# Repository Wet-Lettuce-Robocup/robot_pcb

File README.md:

# Wet Lettuce Robot PCB

Kicad design file for the Wet Lettuce RoboCup Junior International robot.

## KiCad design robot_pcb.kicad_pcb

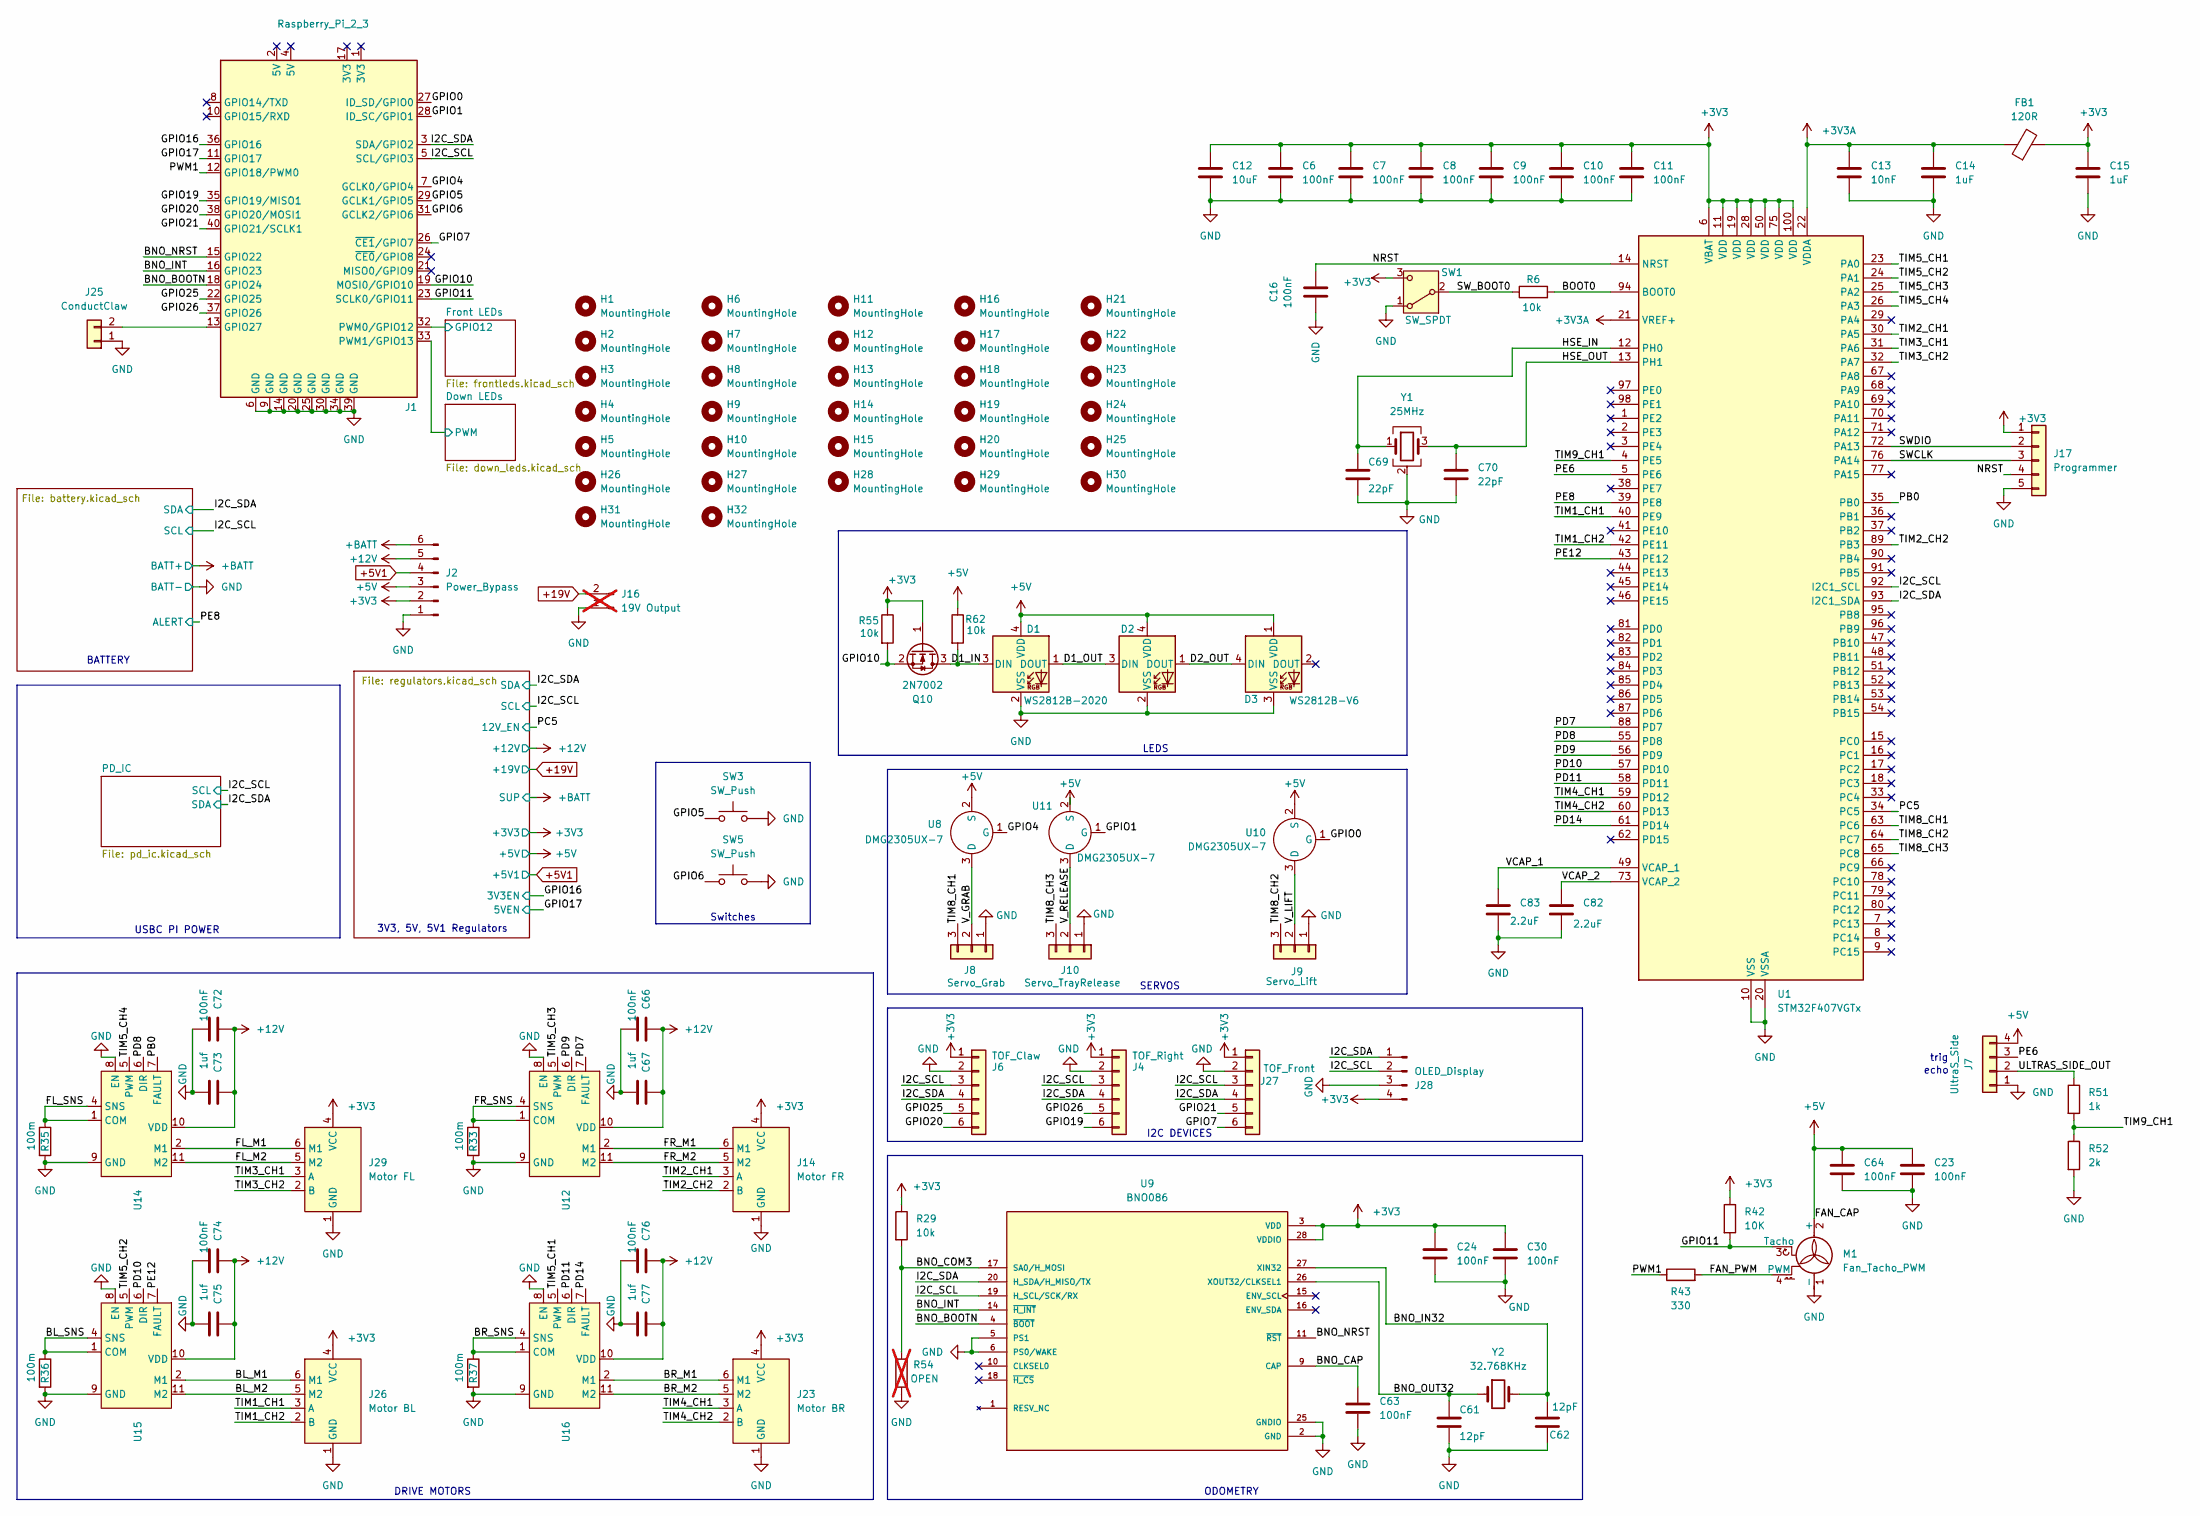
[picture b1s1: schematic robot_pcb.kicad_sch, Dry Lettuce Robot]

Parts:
C6, C7, C8, C9, C10, C11, C16, C23, C24, C30, C63, C64: 100nF; C_0402_1005Metric; LCSC C307331
C12: 10uF; C_0603_1608Metric; LCSC C96446
C13: 10nF; C_0402_1005Metric; LCSC C15195
C14, C15: 1uF; C_0402_1005Metric; LCSC C52923
C61, C62: 12pF; C_0402_1005Metric; LCSC C76948
C66, C72, C74, C76: 100nF; C_0603_1608Metric; LCSC C14663
C67, C73, C75, C77: 1uf; C_0603_1608Metric; LCSC C29936
C69, C70: 22pF; C_0402_1005Metric; LCSC C76960
C82, C83: 2.2uF; C_0603_1608Metric; LCSC C23630
D1, D2: WS2812B-2020; LED_WS2812B-2020_PLCC4_2.0x2.0mm; LCSC C965555
D3: WS2812B-V6; LED_WS2812B_PLCC4_5.0x5.0mm_P3.2mm; LCSC C52917433
FB1: 120R; L_0603_1608Metric; LCSC C113030
H1, H2, H3, H4, H13, H14, H15, H20, H21, H22, H23, H30: MountingHole; MountingHole_3.2mm_M3_DIN965_Pad_TopBottom
H5, H6, H7, H8, H18, H19, H28, H29: MountingHole; MountingHole_2.2mm_M2_DIN965_Pad_TopBottom
H9, H10, H11, H12, H16, H17, H24, H25, H26, H27, H31, H32: MountingHole; MountingHole_2.7mm_M2.5_DIN965_Pad_TopBottom
J1: Raspberry_Pi_2_3; PinHeader_2x20_P2.54mm_Vertical; LCSC C50980
J2: Power_Bypass; PinHeader_1x06_P2.54mm_Vertical; LCSC C52016393
J4: TOF_Right; JST_PH_B6B-PH-K_1x06_P2.00mm_Vertical; LCSC C495261
J6: TOF_Claw; JST_PH_B6B-PH-K_1x06_P2.00mm_Vertical; LCSC C495261
J7: UltraS_Side; PinHeader_1x04_P2.54mm_Vertical; LCSC C541851
J8: Servo_Grab; JST_PH_B3B-PH-K_1x03_P2.00mm_Vertical; LCSC C158004
J9: Servo_Lift; JST_PH_B3B-PH-K_1x03_P2.00mm_Vertical; LCSC C158004
J10: Servo_TrayRelease; JST_PH_B3B-PH-K_1x03_P2.00mm_Vertical; LCSC C158004
J14: Motor FR; JST_PH_S6B-PH-K_1x06_P2.00mm_Horizontal; LCSC C157920
J16: 19V Output; JST_VH_B2PS-VH_1x02_P3.96mm_Horizontal; LCSC C158007; not fitted
J17: Programmer; PinHeader_1x05_P2.54mm_Vertical; LCSC C42431835
J23: Motor BR; JST_PH_S6B-PH-K_1x06_P2.00mm_Horizontal; LCSC C157920
J25: ConductClaw; JST_PH_B2B-PH-K_1x02_P2.00mm_Vertical; LCSC C5251182
J26: Motor BL; JST_PH_S6B-PH-K_1x06_P2.00mm_Horizontal; LCSC C157920
J27: TOF_Front; JST_PH_B6B-PH-K_1x06_P2.00mm_Vertical; LCSC C495261
J28: OLED_Display; OLED_small; LCSC C2718488
J29: Motor FL; JST_PH_S6B-PH-K_1x06_P2.00mm_Horizontal; LCSC C157920
M1: Fan_Tacho_PWM; FanPinHeader_1x04_P2.54mm_Vertical; LCSC C240840
Q10: 2N7002; SOT-23; LCSC C65189
R6, R29, R55, R62: 10k; R_0402_1005Metric; LCSC C60490
R33, R35, R36, R37: 100m; R_1206_3216Metric; LCSC C3033268
R42: 10K; R_0402_1005Metric; LCSC C60490
R43: 330; R_0402_1005Metric; LCSC C105875
R51: 1k; R_0603_1608Metric; LCSC C22548
R52: 2k; R_0603_1608Metric; LCSC C105576
R54: OPEN; R_0402_1005Metric; not fitted
SW1: SW_SPDT; SW_Slide_SPDT_Straight_CK_OS102011MS2Q; LCSC C221829
SW3, SW5: SW_Push; SW_Push_1P1T_NO_CK_new; LCSC C431539
U1: STM32F407VGTx; LQFP-100_14x14mm_P0.5mm; LCSC C720656
U8, U10, U11: DMG2305UX-7; TSOT-23; LCSC C150470
U9: BNO086; IC_BNO086; PARTREV v1.17; LCSC C5264422
U12, U14, U15, U16: Maxim_TDFN-12-1EP_3x3mm_P0.5mm_EP1.7x2.5mm; LCSC C194048
Y1: 25MHz; Crystal_SMD_3225-4Pin_3.2x2.5mm; LCSC C5444544
Y2: 32.768KHz; Crystal_SMD_3215-2Pin_3.2x1.5mm; LCSC C99010

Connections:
+3V3: C6.1, C7.1, C8.1, C9.1, C10.1, C11.1, C12.1, C15.1, C24.1, C30.1, FB1.2, J2.2, J4.1, J6.1, J14.4 (VCC), J17.1, J23.4 (VCC), J26.4 (VCC), J27.1, J28.4, J29.4 (VCC), Q10.1 (G), R29.1, R42.1, R55.1, SW1.3 (C), U1.6 (VBAT), U1.11 (VDD), U1.19 (VDD), U1.28 (VDD), U1.50 (VDD), U1.75 (VDD), U1.100 (VDD), U9.3 (VDD), U9.28 (VDDIO); also elsewhere on the board
+3V3A: C13.1, C14.1, FB1.1, U1.21 (VREF+), U1.22 (VDDA)
+5V: C23.1, C64.1, D1.4 (VDD), D2.4 (VDD), D3.1 (VDD), J2.3, J7.4, M1.2 (+), R62.1, U8.2 (S), U10.2 (S), U11.2 (S); also elsewhere on the board
+5V1: J2.4; also elsewhere on the board
+12V: C66.1, C67.1, C72.1, C73.1, C74.1, C75.1, C76.1, C77.1, J2.5, U12.3 (VDD), U12.10 (VDD), U14.3 (VDD), U14.10 (VDD), U15.3 (VDD), U15.10 (VDD), U16.3 (VDD), U16.10 (VDD); also elsewhere on the board
+19V: J16.2; also elsewhere on the board
+BATT: J2.6; also elsewhere on the board
/BL_M1: J26.6 (M1), U15.2 (M1)
/BL_M2: J26.5 (M2), U15.11 (M2)
/BL_SNS: R36.1, U15.1 (COM), U15.4 (SNS), U15.12 (COM)
/BNO_BOOTN: J1.18 (GPIO24), U9.4 (~BOOT)
/BNO_CAP: C63.1, U9.9 (CAP)
/BNO_COM3: R29.2, R54.1, U9.17 (SA0/H_MOSI)
/BNO_IN32: C62.1, U9.27 (XIN32), Y2.2
/BNO_INT: J1.16 (GPIO23), U9.14 (~H_INT)
/BNO_NRST: J1.15 (GPIO22), U9.11 (~RST)
/BNO_OUT32: C61.1, U9.26 (XOUT32/CLKSEL1), Y2.1
/BOOT0: R6.2, U1.94 (BOOT0)
/BR_M1: J23.6 (M1), U16.2 (M1)
/BR_M2: J23.5 (M2), U16.11 (M2)
/BR_SNS: R37.1, U16.1 (COM), U16.4 (SNS), U16.12 (COM)
/D1_IN: D1.3 (DIN), Q10.3 (D), R62.2
/D1_OUT: D1.1 (DOUT), D2.3 (DIN)
/D2_OUT: D2.1 (DOUT), D3.4 (DIN)
/Down LEDs/PWM: J1.33 (PWM1/GPIO13); also elsewhere on the board
/FAN_PWM: M1.4 (PWM), R43.2
/FL_M1: J29.6 (M1), U14.2 (M1)
/FL_M2: J29.5 (M2), U14.11 (M2)
/FL_SNS: R35.1, U14.1 (COM), U14.4 (SNS), U14.12 (COM)
/FR_M1: J14.6 (M1), U12.2 (M1)
/FR_M2: J14.5 (M2), U12.11 (M2)
/FR_SNS: R33.1, U12.1 (COM), U12.4 (SNS), U12.12 (COM)
/Front LEDs/GPIO12: J1.32 (PWM0/GPIO12); also elsewhere on the board
/GPIO0: J1.27 (ID_SD/GPIO0), U10.1 (G)
/GPIO1: J1.28 (ID_SC/GPIO1), U11.1 (G)
/GPIO4: J1.7 (GCLK0/GPIO4), U8.1 (G)
/GPIO5: J1.29 (GCLK1/GPIO5), SW3.1
/GPIO6: J1.31 (GCLK2/GPIO6), SW5.1
/GPIO7: J1.26 (~CE1/GPIO7), J27.6
/GPIO10: J1.19 (MOSI0/GPIO10), Q10.2 (S), R55.2
/GPIO11: J1.23 (SCLK0/GPIO11), M1.3 (Tacho), R42.2
/GPIO16: J1.36 (GPIO16); also elsewhere on the board
/GPIO17: J1.11 (GPIO17); also elsewhere on the board
/GPIO19: J1.35 (GPIO19/MISO1), J4.6
/GPIO20: J1.38 (GPIO20/MOSI1), J6.6
/GPIO21: J1.40 (GPIO21/SCLK1), J27.5
/GPIO25: J1.22 (GPIO25), J6.5
/GPIO26: J1.37 (GPIO26), J4.5
/HSE_IN: C69.1, U1.12 (PH0), Y1.1
/HSE_OUT: C70.1, U1.13 (PH1), Y1.3
/I2C_SCL: J1.5 (SCL/GPIO3), J4.3, J6.3, J27.3, J28.2, U1.92 (I2C1_SCL), U9.19 (H_SCL/SCK/RX); also elsewhere on the board
/I2C_SDA: J1.3 (SDA/GPIO2), J4.4, J6.4, J27.4, J28.1, U1.93 (I2C1_SDA), U9.20 (H_SDA/H_MISO/TX); also elsewhere on the board
/NRST: C16.2, J17.4, U1.14 (NRST)
/PB0: U1.35 (PB0), U14.7 (FAULT)
/PC5: U1.34 (PC5); also elsewhere on the board
/PD7: U1.88 (PD7), U12.7 (FAULT)
/PD8: U1.55 (PD8), U14.6 (DIR)
/PD9: U1.56 (PD9), U12.6 (DIR)
/PD10: U1.57 (PD10), U15.6 (DIR)
/PD11: U1.58 (PD11), U16.6 (DIR)
/PD14: U1.61 (PD14), U16.7 (FAULT)
/PE6: J7.3, U1.5 (PE6)
/PE8: U1.39 (PE8); also elsewhere on the board
/PE12: U1.43 (PE12), U15.7 (FAULT)
/PWM1: J1.12 (GPIO18/PWM0), R43.1
/SWCLK: J17.3, U1.76 (PA14)
/SWDIO: J17.2, U1.72 (PA13)
/SW_BOOT0: R6.1, SW1.2 (B)
/TIM1_CH1: J26.3 (A), U1.40 (PE9)
/TIM1_CH2: J26.2 (B), U1.42 (PE11)
/TIM2_CH1: J14.3 (A), U1.30 (PA5)
/TIM2_CH2: J14.2 (B), U1.89 (PB3)
/TIM3_CH1: J29.3 (A), U1.31 (PA6)
/TIM3_CH2: J29.2 (B), U1.32 (PA7)
/TIM4_CH1: J23.3 (A), U1.59 (PD12)
/TIM4_CH2: J23.2 (B), U1.60 (PD13)
/TIM5_CH1: U1.23 (PA0), U16.5 (PWM)
/TIM5_CH2: U1.24 (PA1), U15.5 (PWM)
/TIM5_CH3: U1.25 (PA2), U12.5 (PWM)
/TIM5_CH4: U1.26 (PA3), U14.5 (PWM)
/TIM8_CH1: J8.3, U1.63 (PC6)
/TIM8_CH2: J9.3, U1.64 (PC7)
/TIM8_CH3: J10.3, U1.65 (PC8)
/TIM9_CH1: R51.2, R52.1, U1.4 (PE5)
/ULTRAS_SIDE_OUT: J7.2, R51.1
/VCAP_1: C83.1, U1.49 (VCAP_1)
/VCAP_2: C82.1, U1.73 (VCAP_2)
/V_GRAB: J8.2, U8.3 (D)
/V_LIFT: J9.2, U10.3 (D)
/V_RELEASE: J10.2, U11.3 (D)
GND: C6.2, C7.2, C8.2, C9.2, C10.2, C11.2, C12.2, C13.2, C14.2, C15.2, C16.1, C23.2, C24.2, C30.2, C61.2, C62.2, C63.2, C64.2, C66.2, C67.2, C69.2, C70.2, C72.2, C73.2, C74.2, C75.2, C76.2, C77.2, C82.2, C83.2, D1.2 (VSS), D2.2 (VSS), D3.3 (VSS), J1.6 (GND), J1.9 (GND), J1.14 (GND), J1.20 (GND), J1.25 (GND), J1.30 (GND), J1.34 (GND), J1.39 (GND), J2.1, J4.2, J6.2, J7.1, J8.1, J9.1, J10.1, J14.1 (GND), J16.1, J17.5, J23.1 (GND), J25.1, J26.1 (GND), J27.2, J28.3, J29.1 (GND), M1.1 (-), R33.2, R35.2, R36.2, R37.2, R52.2, R54.2, SW1.1 (A), SW3.2, SW5.2, U1.10 (VSS), U1.20 (VSSA), U1.27 (VSS), U1.74 (VSS), U1.99 (VSS), U9.2 (GND), U9.5 (PS1), U9.6 (PS0/WAKE), U9.25 (GNDIO), U12.8 (EN), U12.9 (GND), U12.13 (PAD), U14.8 (EN), U14.9 (GND), U14.13 (PAD), U15.8 (EN), U15.9 (GND), U15.13 (PAD), U16.8 (EN), U16.9 (GND), U16.13 (PAD), Y1.2 (G), Y1.4 (G); also elsewhere on the board
unnamed: J1.13 (GPIO27), J25.2

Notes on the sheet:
LEDS
ODOMETRY
trig
SERVOS
USBC PI POWER
DRIVE MOTORS
BATTERY
3V3, 5V, 5V1 Regulators
Switches
I2C DEVICES
echo

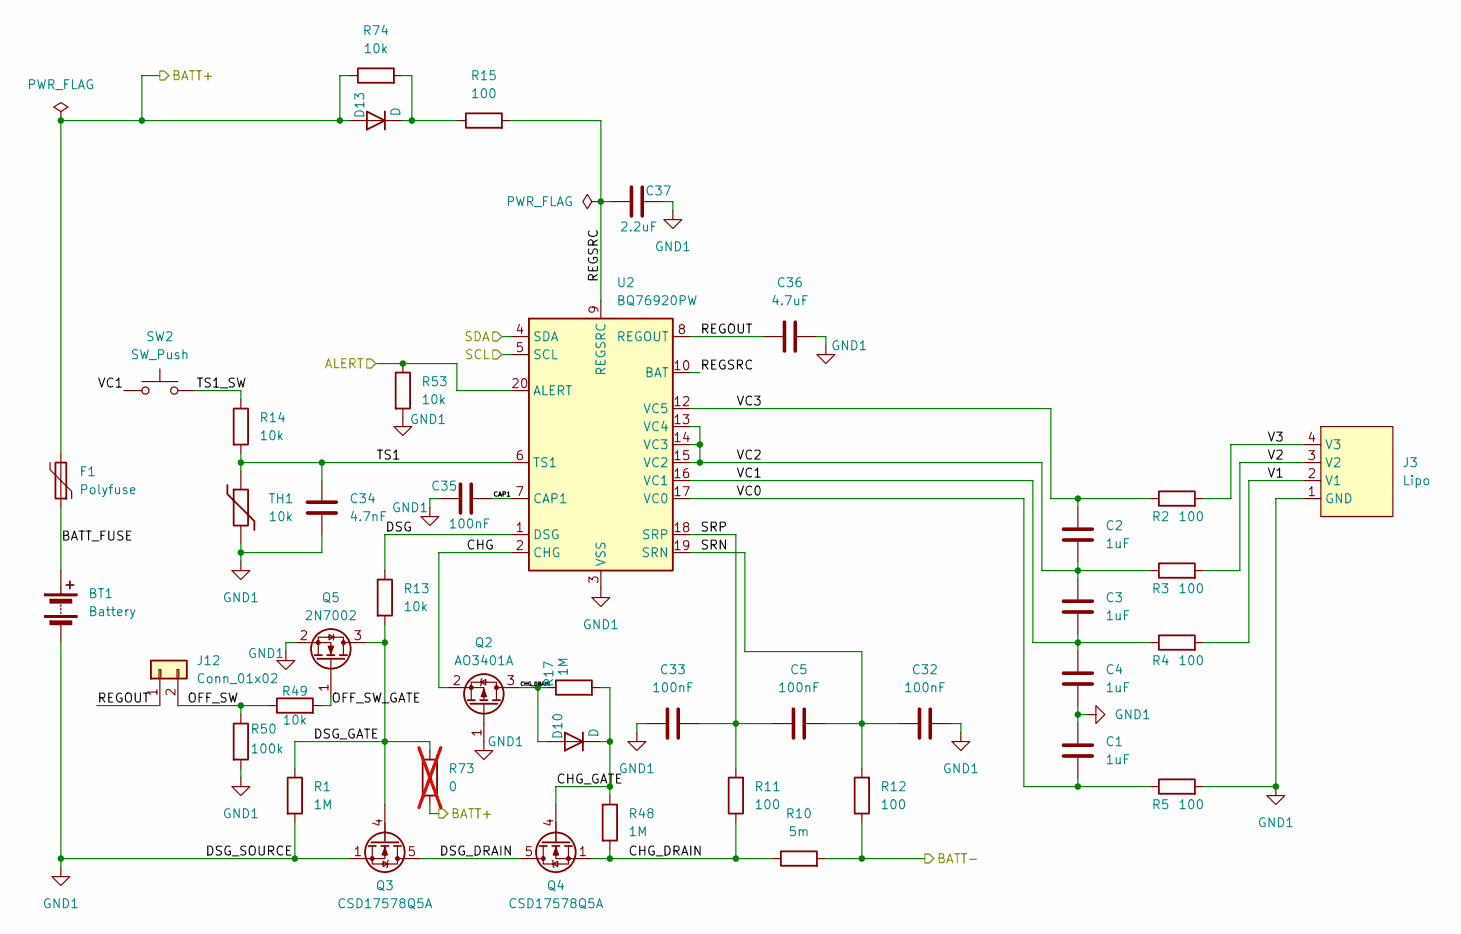
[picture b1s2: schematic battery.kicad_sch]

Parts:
BT1: Battery; AMASS_XT60-M_1x02_P7.20mm_Vertical; LCSC C98733
C1, C2, C3, C4: 1uF; C_0402_1005Metric; LCSC C52923
C5, C32, C33, C35: 100nF; C_0402_1005Metric; LCSC C307331
C34: 4.7nF; C_0402_1005Metric; LCSC C84705
C36: 4.7uF; C_0603_1608Metric; LCSC C69335
C37: 2.2uF; C_0402_1005Metric; LCSC C307418
D10, D13: D; D_0603_1608Metric; LCSC C35621074
F1: Polyfuse; Fuse_Bourns_MF-RG900; LCSC C3762600
J3: Lipo; JST_XH_B4B-XH-A_1x04_P2.50mm_Vertical; LCSC C594232
J12: Conn_01x02; JST_PH_S2B-PH-K_1x02_P2.00mm_Horizontal; LCSC C173752
Q2: AO3401A; SOT-23; LCSC C15127
Q3, Q4: CSD17578Q5A; TDSON-8-1; LCSC C2871447
Q5: 2N7002; SOT-23; LCSC C65189
R1, R17, R48: 1M; R_0402_1005Metric; LCSC C138033
R2, R3, R4, R5: 100; R_0805_2012Metric; LCSC C105577
R10: 5m; R_2512_6332Metric; LCSC C2903482
R11, R12: 100; R_0603_1608Metric; LCSC C105588
R13, R14, R49, R53, R74: 10k; R_0402_1005Metric; LCSC C60490
R15: 100; R_1206_3216Metric; LCSC C2907369
R50: 100k; R_0402_1005Metric; LCSC C60491
R73: 0; R_0402_1005Metric; LCSC C60490; not fitted
SW2: SW_Push; SW_Push_1P1T_NO_CK_new; LCSC C431539
TH1: 10k; R_0402_1005Metric; LCSC C209959
U2: BQ76920PW; TSSOP-20_4.4x6.5mm_P0.65mm; LCSC C601650

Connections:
+BATT: D13.2 (A), F1.2, R73.2, R74.1; also elsewhere on the board
/Battery/BATT_FUSE: BT1.1 (+), F1.1
/Battery/CAP1: C35.2, U2.7 (CAP1)
/Battery/CHG: Q2.2 (S), U2.2 (CHG)
/Battery/CHG_DRAIN: D10.2 (A), Q2.3 (D), Q4.1 (S), Q4.2 (S), Q4.3 (S), R10.1, R11.1, R17.1, R48.2
/Battery/CHG_GATE: D10.1 (K), Q4.4 (G), R17.2, R48.1
/Battery/DSG: R13.1, U2.1 (DSG)
/Battery/DSG_DRAIN: Q3.5 (D), Q4.5 (D)
/Battery/DSG_GATE: Q3.4 (G), Q5.3 (D), R1.1, R13.2, R73.1
/Battery/OFF_SW: J12.2, R49.1, R50.1
/Battery/OFF_SW_GATE: Q5.1 (G), R49.2
/Battery/REGOUT: C36.1, J12.1, U2.8 (REGOUT)
/Battery/REGSRC: C37.1, R15.2, U2.9 (REGSRC), U2.10 (BAT)
/Battery/SRN: C5.2, C32.1, R12.2, U2.19 (SRN)
/Battery/SRP: C5.1, C33.2, R11.2, U2.18 (SRP)
/Battery/TS1: C34.1, R14.2, TH1.1, U2.6 (TS1)
/Battery/TS1_SW: R14.1, SW2.2
/Battery/V1: J3.2 (V1), R4.2
/Battery/V2: J3.3 (V2), R3.2
/Battery/V3: J3.4 (V3), R2.2
/Battery/VC0: C1.2, R5.1, U2.17 (VC0)
/Battery/VC1: C3.2, C4.1, R4.1, SW2.1, U2.16 (VC1)
/Battery/VC2: C2.2, C3.1, R3.1, U2.13 (VC4), U2.14 (VC3), U2.15 (VC2)
/Battery/VC3: C2.1, R2.1, U2.12 (VC5)
/I2C_SCL: U2.5 (SCL); also elsewhere on the board
/I2C_SDA: U2.4 (SDA); also elsewhere on the board
/PE8: R53.1, U2.20 (ALERT); also elsewhere on the board
GND: R10.2, R12.1; also elsewhere on the board
GND1: BT1.2 (-), C1.1, C4.2, C32.2, C33.1, C34.2, C35.1, C36.2, C37.2, J3.1 (GND), Q2.1 (G), Q3.1 (S), Q3.2 (S), Q3.3 (S), Q5.2 (S), R1.2, R5.2, R50.2, R53.2, TH1.2, U2.3 (VSS)
unnamed: D13.1 (K), R15.1, R74.2

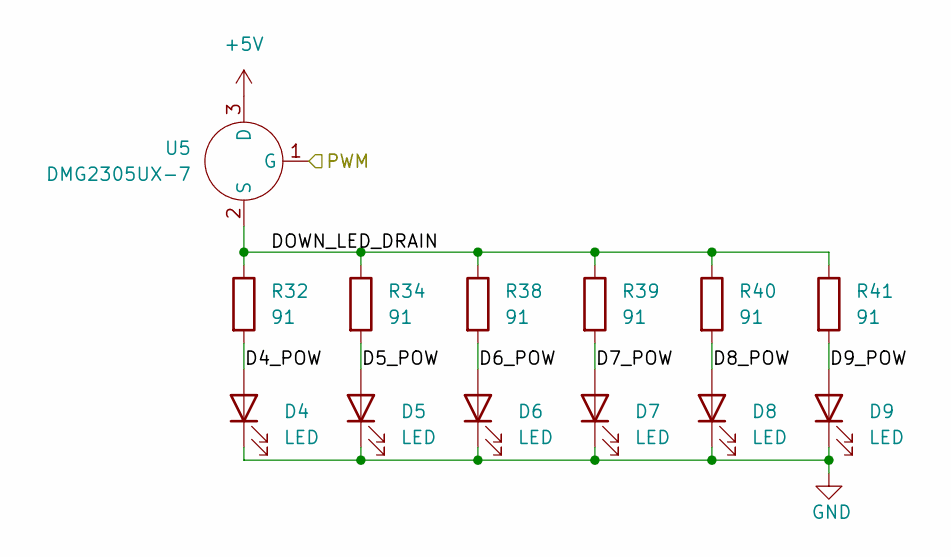
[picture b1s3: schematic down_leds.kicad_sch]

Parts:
D4, D5, D6, D7, D8, D9: LED; LED_PLCC_2835; LCSC C2843876
R32, R34, R38, R39, R40, R41: 91; R_1206_3216Metric; LCSC C5842965
U5: DMG2305UX-7; TSOT-23; LCSC C150470

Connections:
+5V: U5.3 (D); also elsewhere on the board
/Down LEDs/D4_POW: D4.2 (A), R32.2
/Down LEDs/D5_POW: D5.2 (A), R34.2
/Down LEDs/D6_POW: D6.2 (A), R38.2
/Down LEDs/D7_POW: D7.2 (A), R39.2
/Down LEDs/D8_POW: D8.2 (A), R40.2
/Down LEDs/D9_POW: D9.2 (A), R41.2
/Down LEDs/DOWN_LED_DRAIN: R32.1, R34.1, R38.1, R39.1, R40.1, R41.1, U5.2 (S)
/Down LEDs/PWM: U5.1 (G); also elsewhere on the board
GND: D4.1 (K), D5.1 (K), D6.1 (K), D7.1 (K), D8.1 (K), D9.1 (K); also elsewhere on the board

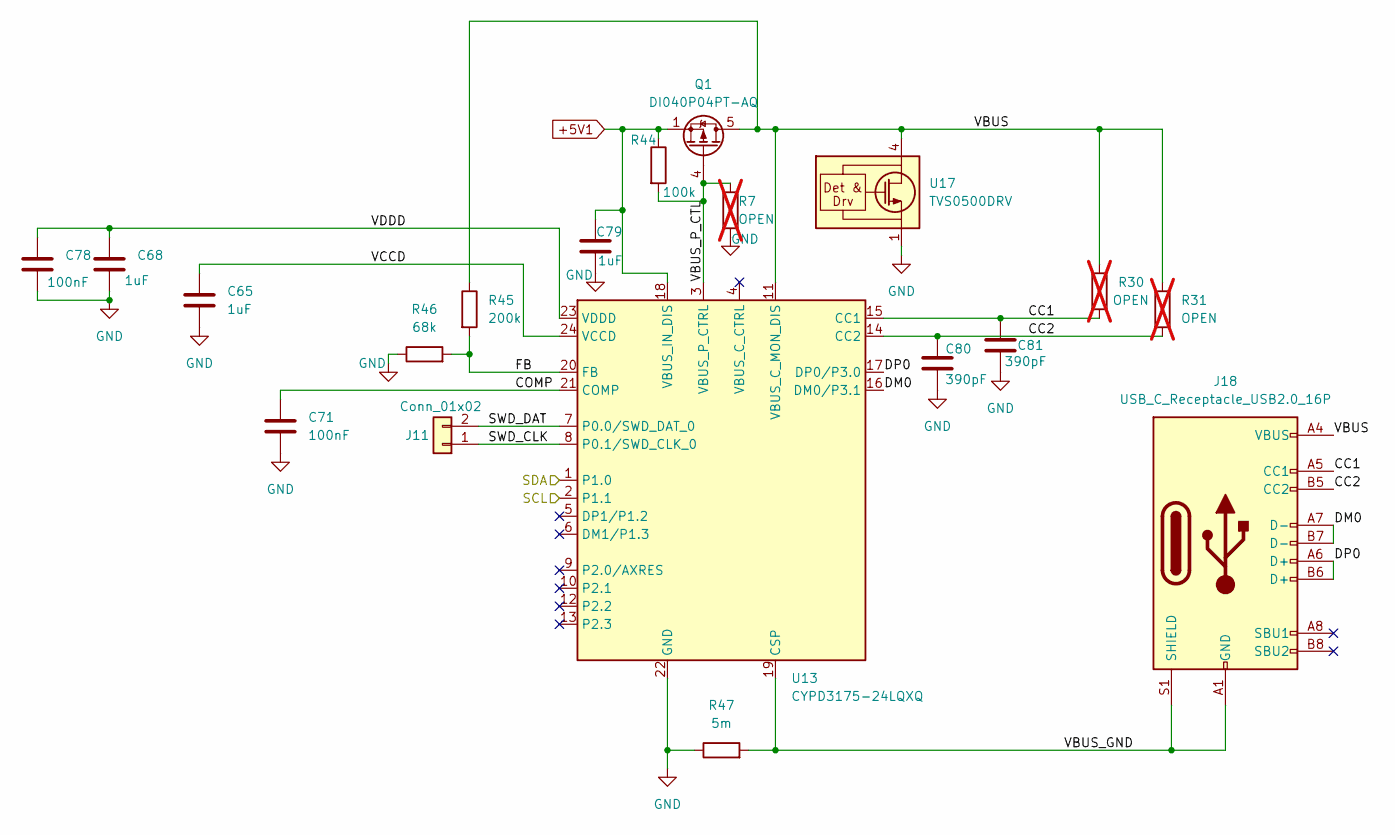
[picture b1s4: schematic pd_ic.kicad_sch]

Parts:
C65, C68, C79: 1uF; C_0402_1005Metric; LCSC C52923
C71, C78: 100nF; C_0402_1005Metric; LCSC C307331
C80, C81: 390pF; C_0402_1005Metric; LCSC C114397
J11: Conn_01x02; PinHeader_1x02_P2.54mm_Vertical; LCSC C52016390
J18: USB_C_Receptacle_USB2.0_16P; USB_C_Receptacle_GCT_USB4105-xx-A_16P_TopMnt_Horizontal; LCSC C3025063
Q1: DI040P04PT-AQ; Vishay_PowerPAK_1212-8_Single; LCSC C6934675
R7, R30, R31: OPEN; R_0402_1005Metric; not fitted
R44: 100k; R_0402_1005Metric; LCSC C60491
R45: 200k; R_0402_1005Metric; LCSC C114763
R46: 68k; R_0402_1005Metric; LCSC C137947
R47: 5m; R_2512_6332Metric; LCSC C2903482
U13: CYPD3175-24LQXQ; QFN-24-1EP_4x4mm_P0.5mm_EP2.75x2.75mm; LCSC C2952419
U17: TVS0500DRV; WSON-6-1EP_2x2mm_P0.65mm_EP1x1.6mm; LCSC C609571

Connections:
+5V1: C79.1, Q1.1 (S), Q1.2 (S), Q1.3 (S), R44.1, U13.18 (VBUS_IN_DIS); also elsewhere on the board
/I2C_SCL: U13.2 (P1.1); also elsewhere on the board
/I2C_SDA: U13.1 (P1.0); also elsewhere on the board
/PD_IC/CC1: C81.1, J18.A5 (CC1), R30.2, U13.15 (CC1)
/PD_IC/CC2: C80.1, J18.B5 (CC2), R31.2, U13.14 (CC2)
/PD_IC/COMP: C71.1, U13.21 (COMP)
/PD_IC/DM0: J18.A7 (D-), J18.B7 (D-), U13.16 (DM0/P3.1)
/PD_IC/DP0: J18.A6 (D+), J18.B6 (D+), U13.17 (DP0/P3.0)
/PD_IC/FB: R45.2, R46.2, U13.20 (FB)
/PD_IC/SWD_CLK: J11.1, U13.8 (P0.1/SWD_CLK_0)
/PD_IC/SWD_DAT: J11.2, U13.7 (P0.0/SWD_DAT_0)
/PD_IC/VBUS: J18.A4 (VBUS), J18.A9 (VBUS), J18.B4 (VBUS), J18.B9 (VBUS), Q1.5 (D), R30.1, R31.1, R45.1, U13.11 (VBUS_C_MON_DIS), U17.4 (IN), U17.5 (IN), U17.6 (IN)
/PD_IC/VBUS_GND: J18.A1 (GND), J18.A12 (GND), J18.B1 (GND), J18.B12 (GND), J18.S1 (SHIELD), R47.2, U13.19 (CSP)
/PD_IC/VBUS_P_CTL: Q1.4 (G), R7.1, R44.2, U13.3 (VBUS_P_CTRL)
/PD_IC/VCCD: C65.1, U13.24 (VCCD)
/PD_IC/VDDD: C68.1, C78.1, U13.23 (VDDD)
GND: C65.2, C68.2, C71.2, C78.2, C79.2, C80.2, C81.2, R7.2, R46.1, R47.1, U13.22 (GND), U13.25 (GND), U17.1 (GND), U17.2 (GND), U17.3 (GND), U17.7 (GND); also elsewhere on the board

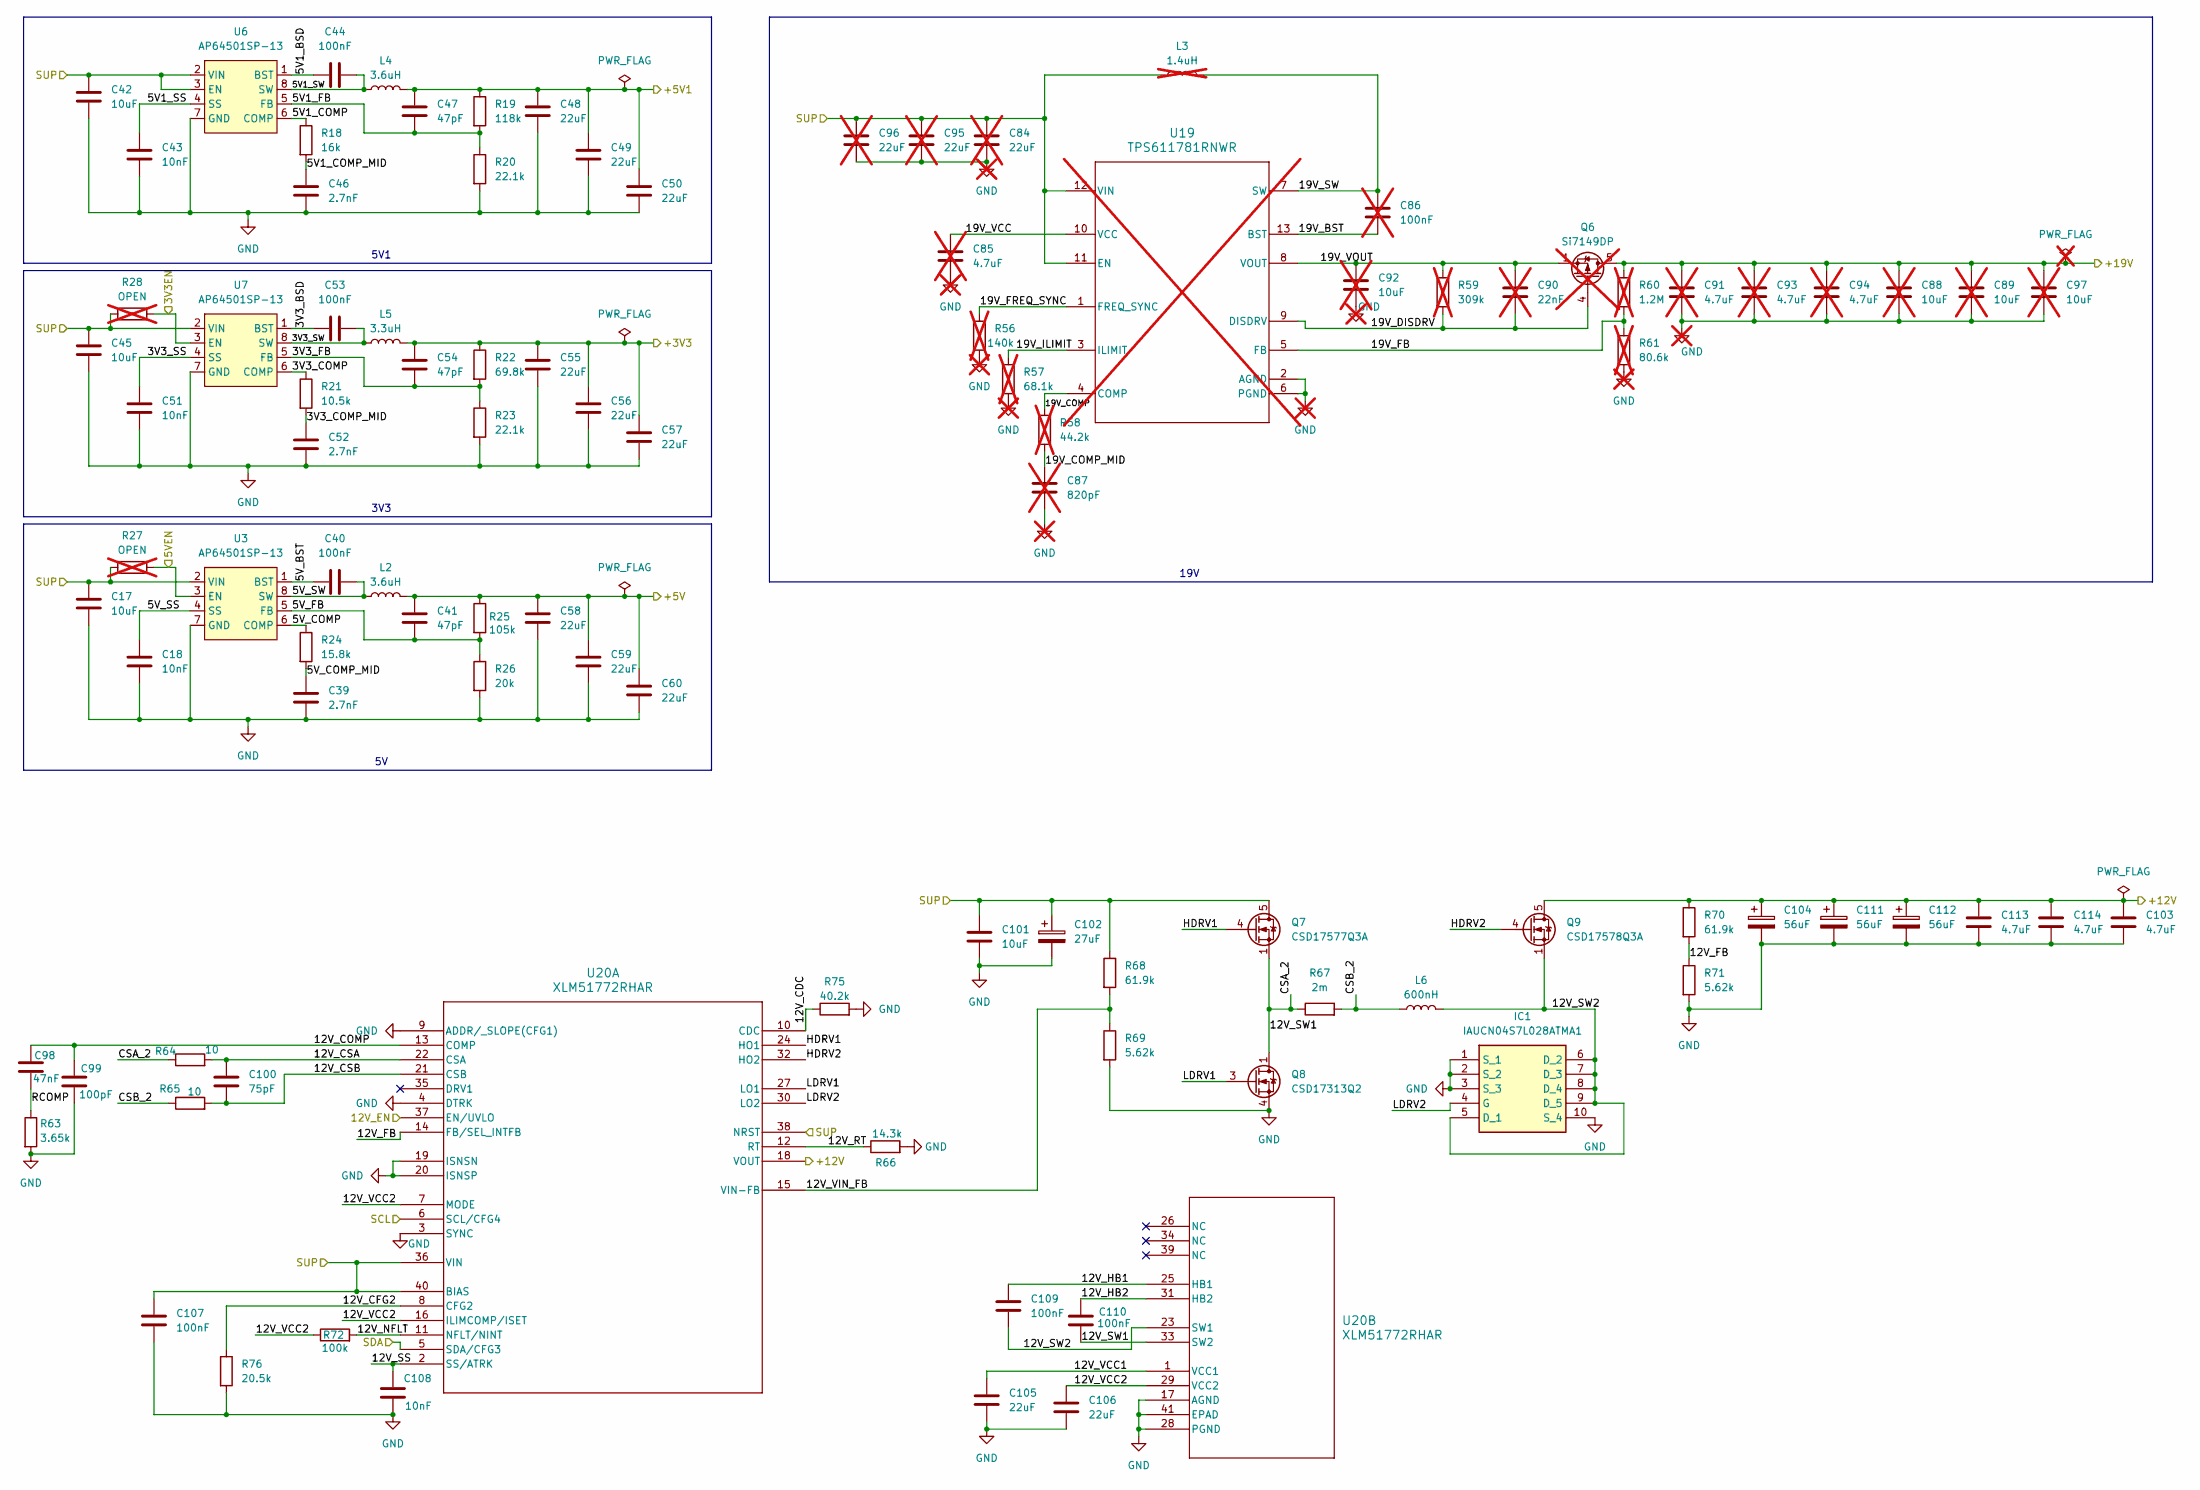
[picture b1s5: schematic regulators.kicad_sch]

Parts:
C17, C42, C45: 10uF; C_0402_1005Metric; LCSC C315248
C18, C43, C51, C108: 10nF; C_0402_1005Metric; LCSC C15195
C39, C46, C52: 2.7nF; C_0402_1005Metric; LCSC C84704
C40, C44, C53, C107, C109, C110: 100nF; C_0402_1005Metric; LCSC C307331
C41, C47, C54: 47pF; C_0402_1005Metric; LCSC C60137
C48, C49, C50, C55, C56, C57, C58, C59, C60: 22uF; C_0805_2012Metric; LCSC C602037
C84, C95, C96: 22uF; C_1210_3225Metric; LCSC C309062; not fitted
C85: 4.7uF; C_0402_1005Metric; LCSC C6119795; not fitted
C86: 100nF; C_0402_1005Metric; LCSC C307331; not fitted
C87: 820pF; C_0402_1005Metric; LCSC C107031; not fitted
C88, C89, C92, C97: 10uF; C_1210_3225Metric; LCSC C138687; not fitted
C90: 22nF; C_0805_2012Metric; LCSC C107147; not fitted
C91, C93, C94: 4.7uF; C_1206_3216Metric; LCSC C51205; not fitted
C98: 47nF; C_0402_1005Metric; LCSC C272875
C99: 100pF; C_0402_1005Metric; LCSC C106200
C100: 75pF; C_0402_1005Metric; LCSC C107010
C101: 10uF; C_0805_2012Metric; LCSC C2932476
C102: 27uF; CP_Elec_5x5.9; LCSC C347564
C103, C113, C114: 4.7uF; C_0805_2012Metric; LCSC C98192
C104, C111, C112: 56uF; CP_Elec_5x5.9; LCSC C2162042
C105, C106: 22uF; C_0603_1608Metric; LCSC C2762594
IC1: IAUCN04S7L028ATMA1; IAUC120N06S5N011ATMA1; Mouser Part Number 726-IAUCN04S7L028ATM
L2, L4: 3.6uH; NRS8040T3R6NJGJ; LCSC C223037
L3: 1.4uH; INDM7570X400N; LCSC C41239516; not fitted
L5: 3.3uH; CYA0630-3.3uH; LCSC C5189747
L6: 600nH; L_Coilcraft_XAL5030-XXX; LCSC C19191623
Q6: Si7149DP; PowerPAK_SO-8_Single; LCSC C553982; not fitted
Q7: CSD17577Q3A; VSON-8_3.3x3.3mm_P0.65mm_NexFET; LCSC C201632
Q8: CSD17313Q2; Texas_DQK; LCSC C2863837
Q9: CSD17578Q3A; VSON-8_3.3x3.3mm_P0.65mm_NexFET; LCSC C205986
R18: 16k; R_0402_1005Metric; LCSC C25759
R19: 118k; R_0402_1005Metric; LCSC C852490
R20, R23: 22.1k; R_0402_1005Metric; LCSC C163478
R21: 10.5k; R_0402_1005Metric; LCSC C5581335
R22: 69.8k; R_0402_1005Metric; LCSC C852893
R24: 15.8k; R_0402_1005Metric; LCSC C26956
R25: 105k; R_0402_1005Metric; LCSC C171671
R26: 20k; R_0402_1005Metric; LCSC C93942
R27, R28: OPEN; R_0603_1608Metric; not fitted
R56: 140k; R_0402_1005Metric; LCSC C114151; not fitted
R57: 68.1k; R_0402_1005Metric; LCSC C11537; not fitted
R58: 44.2k; R_0402_1005Metric; LCSC C25895; not fitted
R59: 309k; R_0402_1005Metric; LCSC C4180598; not fitted
R60: 1.2M; R_0603_1608Metric; LCSC C13315; not fitted
R61: 80.6k; R_0402_1005Metric; LCSC C25921; not fitted
R63: 3.65k; R_0402_1005Metric; LCSC C852768
R64, R65: 10; R_0603_1608Metric; LCSC C109318
R66: 14.3k; R_0402_1005Metric; LCSC C185465
R67: 2m; R_1206_3216Metric; LCSC C92124
R68, R70: 61.9k; R_0402_1005Metric; LCSC C852869
R69, R71: 5.62k; R_0402_1005Metric; LCSC C851068
R72: 100k; R_0402_1005Metric; LCSC C60491
R75: 40.2k; R_0402_1005Metric; LCSC C137983
R76: 20.5k; R_0402_1005Metric; LCSC C185445
U3, U6, U7: AP64501SP-13; SOIC-8-1EP_3.9x4.9mm_P1.27mm_EP2.29x3mm; LCSC C2071517
U19: TPS611781RNWR; RNW0013A; LCSC C2862009; not fitted
U20: XLM51772RHAR; VQFN40_RHA_TEX; LCSC C41383743

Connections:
+3V3: C54.1, C55.1, C56.1, C57.1, L5.2, R22.1; also elsewhere on the board
+5V: C41.1, C58.1, C59.1, C60.1, L2.2, R25.1; also elsewhere on the board
+5V1: C47.1, C48.1, C49.1, C50.1, L4.2, R19.1; also elsewhere on the board
+12V: C103.1, C104.1, C111.1, C112.1, C113.1, C114.1, Q9.5 (D), R70.1, U20.18 (VOUT); also elsewhere on the board
+19V: C88.1, C89.1, C91.1, C93.1, C94.1, C97.1, Q6.5 (D), R60.1; also elsewhere on the board
+BATT: C17.1, C42.1, C45.1, C84.1, C95.1, C96.1, C101.1, C102.1, C107.1, L3.1, Q7.5 (D), R27.1, R28.1, R68.1, U3.2 (VIN), U6.2 (VIN), U6.3 (EN), U7.2 (VIN), U19.11 (EN), U19.12 (VIN), U20.36 (VIN), U20.38 (NRST), U20.40 (BIAS); also elsewhere on the board
/GPIO16: R28.2, U7.3 (EN); also elsewhere on the board
/GPIO17: R27.2, U3.3 (EN); also elsewhere on the board
/I2C_SCL: U20.6 (SCL/CFG4); also elsewhere on the board
/I2C_SDA: U20.5 (SDA/CFG3); also elsewhere on the board
/PC5: U20.37 (EN/UVLO); also elsewhere on the board
/Regulators/3V3_BSD: C53.1, U7.1 (BST)
/Regulators/3V3_COMP: R21.1, U7.6 (COMP)
/Regulators/3V3_COMP_MID: C52.1, R21.2
/Regulators/3V3_FB: C54.2, R22.2, R23.1, U7.5 (FB)
/Regulators/3V3_SS: C51.1, U7.4 (SS)
/Regulators/3V3_SW: C53.2, L5.1, U7.8 (SW)
/Regulators/5V1_BSD: C44.1, U6.1 (BST)
/Regulators/5V1_COMP: R18.1, U6.6 (COMP)
/Regulators/5V1_COMP_MID: C46.1, R18.2
/Regulators/5V1_FB: C47.2, R19.2, R20.1, U6.5 (FB)
/Regulators/5V1_SS: C43.1, U6.4 (SS)
/Regulators/5V1_SW: C44.2, L4.1, U6.8 (SW)
/Regulators/5V_BST: C40.1, U3.1 (BST)
/Regulators/5V_COMP: R24.1, U3.6 (COMP)
/Regulators/5V_COMP_MID: C39.1, R24.2
/Regulators/5V_FB: C41.2, R25.2, R26.1, U3.5 (FB)
/Regulators/5V_SS: C18.1, U3.4 (SS)
/Regulators/5V_SW: C40.2, L2.1, U3.8 (SW)
/Regulators/12V_CDC: R75.1, U20.10 (CDC)
/Regulators/12V_CFG2: R76.1, U20.8 (CFG2)
/Regulators/12V_COMP: C98.1, C99.1, U20.13 (COMP)
/Regulators/12V_CSA: C100.1, R64.2, U20.22 (CSA)
/Regulators/12V_CSB: C100.2, R65.2, U20.21 (CSB)
/Regulators/12V_FB: R70.2, R71.1, U20.14 (FB/SEL_INTFB)
/Regulators/12V_HB1: C109.1, U20.25 (HB1)
/Regulators/12V_HB2: C110.1, U20.31 (HB2)
/Regulators/12V_NFLT: R72.2, U20.11 (NFLT/NINT)
/Regulators/12V_RT: R66.1, U20.12 (RT)
/Regulators/12V_SS: C108.1, U20.2 (SS/ATRK)
/Regulators/12V_SW1: C110.2, Q7.1 (S), Q7.2 (S), Q7.3 (S), Q8.1 (D), Q8.2 (D), Q8.5 (D), Q8.6 (D), Q8.8 (D), R64.1, R67.1, U20.33 (SW2)
/Regulators/12V_SW2: C109.2, IC1.5 (D_1), IC1.6 (D_2), IC1.7 (D_3), IC1.8 (D_4), IC1.9 (D_5), L6.2, Q9.1 (S), Q9.2 (S), Q9.3 (S), U20.23 (SW1)
/Regulators/12V_VCC1: C105.1, U20.1 (VCC1)
/Regulators/12V_VCC2: C106.1, R72.1, U20.7 (MODE), U20.16 (ILIMCOMP/ISET), U20.29 (VCC2)
/Regulators/12V_VIN_FB: R68.2, R69.1, U20.15 (VIN-FB)
/Regulators/19V_BST: C86.2, U19.13 (BST)
/Regulators/19V_COMP: R58.1, U19.4 (COMP)
/Regulators/19V_COMP_MID: C87.1, R58.2
/Regulators/19V_DISDRV: C90.2, Q6.4 (G), R59.2, U19.9 (DISDRV)
/Regulators/19V_FB: R60.2, R61.1, U19.5 (FB)
/Regulators/19V_FREQ_SYNC: R56.1, U19.1 (FREQ_SYNC)
/Regulators/19V_ILIMIT: R57.1, U19.3 (ILIMIT)
/Regulators/19V_SW: C86.1, L3.2, U19.7 (SW)
/Regulators/19V_VCC: C85.1, U19.10 (VCC)
/Regulators/19V_VOUT: C90.1, C92.1, Q6.1 (S), Q6.2 (S), Q6.3 (S), R59.1, U19.8 (VOUT)
/Regulators/CSB_2: L6.1, R65.1, R67.2
/Regulators/HDRV1: Q7.4 (G), U20.24 (HO1)
/Regulators/HDRV2: Q9.4 (G), U20.32 (HO2)
/Regulators/LDRV1: Q8.3 (G), U20.27 (LO1)
/Regulators/LDRV2: IC1.4 (G), U20.30 (LO2)
/Regulators/RCOMP: C98.2, R63.1
GND: C17.2, C18.2, C39.2, C42.2, C43.2, C45.2, C46.2, C48.2, C49.2, C50.2, C51.2, C52.2, C55.2, C56.2, C57.2, C58.2, C59.2, C60.2, C84.2, C85.2, C87.2, C88.2, C89.2, C91.2, C92.2, C93.2, C94.2, C95.2, C96.2, C97.2, C99.2, C101.2, C102.2, C103.2, C104.2, C105.2, C106.2, C107.2, C108.2, C111.2, C112.2, C113.2, C114.2, IC1.1 (S_1), IC1.2 (S_2), IC1.3 (S_3), IC1.10 (S_4), Q8.4 (S), Q8.7 (S), R20.2, R23.2, R26.2, R56.2, R57.2, R61.2, R63.2, R66.2, R69.2, R71.2, R75.2, R76.2, U3.7 (GND), U3.9 (PAD), U6.7 (GND), U6.9 (PAD), U7.7 (GND), U7.9 (PAD), U19.2 (AGND), U19.6 (PGND), U20.3 (SYNC), U20.4 (DTRK), U20.9 (ADDR/_SLOPE(CFG1)), U20.17 (AGND), U20.19 (ISNSN), U20.20 (ISNSP), U20.28 (PGND), U20.41 (EPAD); also elsewhere on the board

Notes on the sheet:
19V
3V3
5V1
